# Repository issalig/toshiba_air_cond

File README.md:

# toshiba_air_cond
This project implements functions to decode Toshiba AB protocol from indoor units to wired controllers and provides a hardware design for communication.

Gerbers are available but remember if you improve the design please share it, that's how open source works, if you do not want to share, this project is not for you.

I strongly recommend to use [makusets' board](https://github.com/makusets/esphome-toshiba-ab/tree/main/hardware/D1%20mini) instead of my custom hardware.
My hardware is designed assuming a voltage level of the AB line around 15.6V when "1" and 14V when "0". Different voltage values will not work for writing while reading will work.

In particular, this project has been tested with remote control unit RBC-AMT32E and central unit RAV-SM406BTP-E (http://www.toshiba-aircon.co.uk/assets/uploads/product_assets/20131115_IM_1115460101_Standard_Duct_RAV-SM_6BTP-E_EN.pdf)

You can find the service manual from central unit and wired controller here: http://www.toshibaclim.com/Portals/0/Documentation/Manuels%20produits/SM_Gainable_Std-Compact--DI_406566806110614061606_GB.pdf, https://rednux.com/mediafiles/Hersteller/toshiba/Toshiba-Bedienungsanleitung-RBC-AMT32E-Englisch.pdf

## Index

[Software installation](#Software-installation)

[Web Interface](#Web-Interface)

[Home Assistant & MQTT](#Home-Assistant-&-MQTT)

[Hardware Installation](#Hardware-Installation)

[Custom hardware](#Custom-hardware)

[Data format](#Data-format)

[Message types](#Message-types)

[Other info](#Other-info)
 
# Software installation
[Up](#toshiba_air_cond) [Previous](#Index) [Next](#Hardware-Installation)

Code is developed in PlatformIO for ESP8266 and in particular for Wemos D1 mini board. It is basically a WebServer that serves a webpage and communicates with the client by means of WebSockets. It also offers Home Assistant integration and has nice features usch as OTA updates, file uploading, WifiManager and others.

### Dependencies

This project uses libraries and code from different authors, they are installed automatically from platformio.ini file

- [esp8266](https://github.com/esp8266/Arduino)
- [espsoftwareserial](https://github.com/plerup/espsoftwareserial) by Peter Lerup
- [WiFiManager](https://github.com/tzapu/WiFiManager) by tzapu
- [WebSockets](https://github.com/Links2004/arduinoWebSockets) by Links2004
- [ArduinoJson](https://github.com/bblanchon/ArduinoJson) by Benoit Blanchon
- [Adafruit libraries](https://github.com/adafruit) Adafruit SSD1306, Adafruit GFX Library, adafruit/Adafruit AHTX0 and adafruit/Adafruit BMP280
- LittleFS
- [PubSubClient](https://github.com/knolleary/pubsubclient)
- NTPClient

### Compilation
First things first. Compile it with VSCode and upload it to the board with PlatformIO.

Minimal hardware is ESP8266 and the pcb for adapting signal from serial to AB line. 

- ESP8266 (Wemos D1 Mini R2)
- Toshiba AC serial interface (SoftwareSerial D7=RX, D8=TX)
- Optional I2C sensors (shared bus D1=SCL, D2=SDA):
  - AHT20 (temperature + humidity)  [enabled with `#define USE_AHT20`]
  - BMP280 (temperature + pressure) [enabled with `#define USE_BMP280`]
  - BME280 (temperature + humidity + pressure) [enabled with `#define USE_BME280`]
- Optional OLED 128x64 SSD1306 (I2C D1=SCL, D2=SDA)         [`#define USE_SCREEN`]
- Reset / Config button on D4 (WiFiManager AP)
  
To sum up, the following defines are available and features are disabled by commenting its `#define` in  [config.h](https://github.com/issalig/toshiba_air_cond/blob/master/air/config.h)

- `USE_OTA`      OTA updates
- `USE_SCREEN`   OLED status display
- `USE_MQTT`     MQTT + Home Assistant integration
- `USE_AHT20`    AHT20 sensor support
- `USE_BMP280`   BMP280 sensor support

### WiFi setup
Once you have the code uploaded it is time to configure your WiFi. This project makes use of the great WiFiManager library so there is no need to hardcode your WiFi settings.
- Plug you esp board. It will start blinking.
- Connect to **airAP** wifi network from your cellphone or PC.
- Open a browser and the WifiManager will appear.
- Select your WiFi network and the password.
- If everything is correct, airAP shuts down and board connects to your WiFi.
- Connect to your normal WiFi from computer/cellphone.

### Connect
Now the esp8266 is connected to your network and can be reached as http://air.local

### Upload files
Connect to http://air.local/filemanager, type  and upload it.

This will store index.html file and http://air.local should show the main page.
You can use this endpoint to modify the webpage or add more functionality. If you do it please share.

### Delete files
Similarly to upload page you can use http://air.local/filemanager to delete a file.

### OTA and file update
OTA updates are available, so you do not need to unplug the esp everytime you want to flash it. In the Arduino IDE just set Tools->Port->air at xxx.
If you are using PlatformIO it is done in platform.io
Default OTA password is esp8266

```
; OTA upload configuration
upload_protocol = espota
upload_port = air.local        ; Replace with your device's actual IP from OTAName in config.cpp
upload_flags = --auth=esp8266  ; Replace with your OTA password from OTAPassword varialble in config.cpp
```

If you just want to upload individual files you can use http://air.local/edit.html

# Web Interface
[Up](#toshiba_air_cond) [Previous](#Software-Installation) [Next](#Hardware-Installation)

This section describes the features available through the embedded web interface served by the ESP8266 air conditioning controller.

## Access
- URL via mDNS: `http://air.local` (See `mdnsName` in `config.h`)
- HTTP Port: 80
- WebSocket Port: 81

)

## Main Features
1. Control Functions
   - Power ON / OFF
   - Set target temperature (bounded 16–30 °C; internally enforced 18–30 in MQTT handler)
   - Change mode: `cool`, `heat`, `dry`, `fan_only`, `auto`, `off`
   - Change fan speed: `auto`, `low`, `medium`, `high`
   - Save mode

2. Timer
   - ON/OFF Timer. Software based relying only in esp8266

3. Chart
   - Shows current temperature, external temperature and pressure/humidity if sensors are available.

4. System
   - Info: IP, boot time and decoding errors.
   - Sensors: Internal / External AC sensors.
   - Address: Address configuration for master/remote in case your system uses different from default or you want to install different remotes.
   - Mode: 
    - Autonomous mode indicator: Use it if there is no remote connected (sends pings like remotes). It is necessary to have a temperature sensor to report room temperture.
    - Simulation mode indicator: Simulates a physical AC
   - Admin: Upload files. Use it to upload index.html and others.
5. Debug
    - Send RAW messages to AC, i.e., "00 FE 10 02 80 8A E6"
    - Debug output: Shows serial raw and decoded messages
    - Log

6. MQTT Configuration (if `USE_MQTT`)
   - Runtime modification of: host, port, username, password, device name
   - Persisted to `/mqtt_config.json` in LittleFS

# Home Assistant & MQTT
[Up](#toshiba_air_cond) [Previous](#Web-Interface) [Next](#Hardware-Installation)

If `USE_MQTT` is enabled, the device integrates with Home Assistant using MQTT Discovery.

### Discovery
The device automatically publishes configuration to:
`homeassistant/climate/toshiba_ac/config`

### Manual Configuration / Topics
If discovery is not used, here are the available topics:

| Topic Type | Topic Path | Payload / Description |
|---|---|---|
| **Status** | `homeassistant/ac/status/mode` | `cool`, `heat`, `auto`, `fan_only`, `dry`, `off` |
| **Status** | `homeassistant/ac/status/fan_mode` | `auto`, `high`, `medium`, `low` |
| **Status** | `homeassistant/ac/status/temperature` | Target Temperature (e.g. `22`) |
| **Status** | `homeassistant/ac/status/current_temperature` | Room Temperature (e.g. `21.5`) |
| **Command** | `homeassistant/ac/set/mode` | Set mode (same values as status + `on`/`off`) |
| **Command** | `homeassistant/ac/set/fan_mode` | Set fan speed |
| **Command** | `homeassistant/ac/set/temperature` | Set target temperature |

### Configuration
MQTT settings (Broker, User, Password) can be configured via the Web Interface and are saved to `/mqtt_config.json`. The device status (Power, Mode, Fan, Temperature) is periodically published and updated in real-time when changed via Web or Remote.

# Hardware installation
[Up](#toshiba_air_cond) [Previous](#Home-Assistant-&-MQTT) [Next](#Data-acquisition)

You will need an esp8266, a circuit for adapting signals to esp8266, a USB power supply, a a couple of dupont (female) wires.
- Take out the cover of your remote controller
- Loose the screws of AB terminals. **WARNING**: My PCB assumes A is positive and B is negative. If this is not your case you can damage the PCB. (https://github.com/issalig/toshiba_air_cond/discussions/40#discussioncomment-8149607)
- Pass the wires through the ventilation holes of the cover.
- Insert dupont wires on the terminals and screw them again
- Close the cover
- Connect dupont wires to the pcb (A,B)
- Plug the Wemos D1 mini into the pcb
- Power Wemos with usb cable and the led will start blinking (if you have already programmed it)

Just switch it on/off while you are in bed. If you like it just send me a beer and/or improve the project!

# Data acquisition
[Up](#toshiba_air_cond) [Previous](#Hardware-Installation) [Next](#Custom-hardware)

This is how I managed to decode the information from the AB bus. First I plugged a multimeter to check the range of the signal and not fry anything. Then I used a DS0138 oscilloscope to monitor the signal and to guess voltages and baudrate (a resistor divider is suggested in order to lower the voltage). Later, an 8-channel USB logic analyzer (4-5 USD) can be used to capture data into the computer. **REMEMBER** to convert voltages to 0-3.3v before connecting it to logic analyzer or you will make magic smoke. You can use the read circuit below.

To capture data you can use pulseview with uart decoder 2400 bps, 8bits, start, stop, EVEN parity

In case you need it you can install the following packages
```
sudo apt install sigrok-cli
sudo apt install sigrok-firmware-fx2lafw
```

When the data has been validated visually you can use the following command line that reads RX data annotations and print one message per line according to 4th byte (message size).

```
sigrok-cli -P uart:rx=D0:baudrate=2400:parity_type=even -A uart=rx_data -i  YOURFILE  | awk '{pad =" "; b[len%4]=$2; if(len==3) {bytes="0x"b[len];  printf("%s%s%s%s%s%s%s%s",b[0],pad,b[1],pad,b[2],pad,b[3],pad)} if(len>3) {printf("%s%s",$2,pad);} len=len+1; if(len==4+bytes+1) {print "";len=0;bytes=0}}'
```

```
sigrok-cli -d fx2lafw -c samplerate=250000 -t D0=r -P uart:rx=D0:baudrate=2400:parity_type=even  -A uart=rx_data --continuous
```

# Custom hardware
[Up](#toshiba_air_cond) [Previous](#Data-acquisition) [Next](#Data-format)

Note: I strongly recommend to use [makusets board](https://github.com/makusets/esphome-toshiba-ab/tree/main/hardware/D1%20mini) instead of my custom hardware.
My hardware is designed assuming a voltage level of the AB line around 15.6V when "1" and 14V when "0". Different voltage values will not work for writing while reading will work.

I have designed some circuits to read and write the signal

## Read
I will use an optocoupler because it simplifies things and also isolates microcontroller from the rest of the system.

- Air conditioning side:
Voltage is around 15.6 volts when "1" and 14 when "0". A zener diode in reversed position provides 13V reference given that voltage is in the range [14, 15.6] and is > 13V. Thus, the signal is now in the range [1V, 2.6V]. Then, after diode 1N4001 (0.7V drop) voltage is 0.3V .. 1.9V, enough to activate the photodiode (1.2V) when "1" and to not activate it when "0".

IR led from optocouple drops 1.2v, and from signal we have a difference of 15.6V-13V=2.6V, thus 2.6V-1.2V=1.4V/100ohm = 14mA which has a maximum CTR=140%
Ic=3.3, If=14
CTR=Ic/If

```
Type     VZnom  IZT  for  rzjT    rzjk  at  IZK    IR  at  VR
1N4743A  13     19        <10     <100      0.25   <5      9.9
```

Now, let's calculate the resistor value
Izt=19 mA -> 2.6/19=130ohm  P=VI 2.6*19 =52mW

- Microcontroller side: 1k resistor limits the current. ESP8266 max current is 12mA > 3.3/1k = 3.3 mA

```
Air                                         Microcontroller
Conditioner

                          1N4001  _______
  A ---------+----100R ---->|----|       |-------3v3
             |                   | PC817 |
            10k                  |       |
             |                   |       |
  B --->|----+-------------------|_______|------ OUT               
                                             |
     zener 13v                              1k
      1N4743A                                |
                                            GND
             
```

## Write

Write circuit performs similarly to read circuit. 
- When OUT signal is "1", transistor and pullup resistor are "0", thus optocoupler is OFF and voltage is 15.6 (HIGH). 
- When OUT signal is 0, transistor is off and pullup resistor sends 1 and activates optocoupler and zener diode gives 13V (LOW).
Some systems recommend to set the Follower in the remote unit.

Here I attach the datasheets of the components.
https://www.onsemi.com/pub/Collateral/P2N2222A-D.PDF 
https://learnabout-electronics.org/Downloads/PC817%20optocoupler.pdf

```

              3v3                                    1N4001
               |                             |-----+---|<------- A               
              200                 _______    |     |               
               ------------------|       |---|     ^ zener 13v
               /                 | PC817 |         /
 OUT --1k- ---|   2N2222     |---|_______|---1k---| 2N2222
               \             |                     \
               |             |                     |
              GND           GND                    ------------- B

```

## Plan B. (In fact it was plan A but then I managed to decode AB protocol, yeah!)

To solder wires to button pads on the remote controller and close circuit to simulate pressing them (with and optocoupler).

``` 
                       _________
    uc OUT --- 200R----| PC817 |------- PAD+
                 GND---|_______|---4k7--PAD-
                                  
```

ESP8266 high level is 3v3 and the maximum current per pin is 12mA (but we will go safer with 10mA). Thus, the resistor for the IR diode of the optocoupler is 3.3-1.2/10=210 -> 200 ohm. 4k7 is a safe value since we just want continuity.

Following traces from button pads end in 2k resistors that we will use to solder wires. As R46 is common, we can think is button GND
ON button is connected to R25 and R46
Temp down button is connected to R23 adn R46
Temp up button is connected to R24 and R46

# Data format
[Up](#toshiba_air_cond) [Previous](#Custom-hardware) [Next](#Message-types)

Data packages have the following format:

|Source | Dest | Opcode 1  | Data Length | R/W mode | Opcode 2 | Payload | CRC |
|---|---|---|---|---|---|---|---|

Source/Dest (1 byte): 
|#|Description|
|---|---|
|00 | master (central unit) |
|40 | remote controller in the range [0x40..] |
|FE | broadcast |
|F0 | Group
|52 | ?? |

Data length (1 byte)
- Length of data field

R/W mode (1 byte)
|Mode|Desc|
|---|---|
|08 |for Write mode (from remote 40)|
|80 |for Read mode (from master 00)|

Payload can be empty such as in ping message 00 FE 10 02 80 8A E6.

CRC is computed as Checksum8 XOR of all the bytes (Compute it at https://www.scadacore.com/tools/programming-calculators/online-checksum-calculator/)

OpCode1 (byte 2)  indicates the function of the message and OpCode2 (byte 5) specifies the feature or register being targeted.

| OpCode1 | Description | Type | Example |
|---|---|---|---|
| `10` | Ping / Alive | `MSG_MASTER_ALIVE` | `00 FE 10 02 80 8A E6` |
| `11` | Write / Control | `MSG_POWER`, `MSG_SET_...` | `40 00 11 03 08 41 03 18` |
| `15` | Request / Query | `MSG_MODEL_REQUEST`... | `40 F0 15 02 00 08 AF` |
| `17` | Sensor Query | `MSG_SENSOR_QUERY` | `40 00 17 08 08 80 EF 00 2C 08 00 02 1E` |
| `18` | Response / Report | `MSG_MODEL_ANSWER`... | `00 40 18 14 80 08 52 41 56 2d 53 4d 31 31 30 36 42 54 50 2d 45 20 03 37 8e` |
| `1A` | Sensor Answer | `MSG_SENSOR_ANSWER` | `00 40 1A 07 80 EF 80 00 2C 00 2B B5` |
| `1C` | Status | `MSG_STATUS` | `00 FE 1C 0D 80 81 8D AC 00 00 76 00 33 33 01 00 01 B9` |
| `52` | Remote Start | - | - |
| `55` | Remote Temp | `MSG_REMOTE_SENSOR_TEMP` | `40 00 55 05 08 81 00 69 00 F0` |
| `58` | Ext. Status | `MSG_STATUS_EXT` | `00 FE 58 0F 80 81 34 A8 00 00 6C 6D E9 00 55 55 01 00 01 DC` |

| OpCode2 | Description | Type | Example |
|---|---|---|---|
| `02` | DN Codes | `MSG_DN_CODE` | `40 00 15 05 08 02 F5 00 01 AE` |
| `07` | Save Ratio | `MSG_SAVE_RATIO_...` | `00 40 18 03 80 07 4B 97` |
| `08` | Model Info | `MSG_MODEL_...` | `00 40 18 14 80 08 52 41 56 2d 53 4d 31 31 30 36 42 54 50 2d 45 20 03 37 8e` |
| `0A` | Temp Limits | `MSG_TEMP_LIMITS` | `00 40 18 10 80 0A 00 2F 0F 80 6A 80 6A 80 6A 80 6A 04 56 00 B0` |
| `0C` | Pong / Ping | `MSG_REMOTE_PING` | `40 00 15 07 08 0C 81 00 00 48 00 9F` |
| `0D` | Announce | `MSG_ANNOUNCE` | `40 F0 15 02 00 0D AA` |
| `0F` | Setpoints | `MSG_SETPOINT` | `00 40 18 09 80 0F 7A 74 78 78 25 52 05 A2` |
| `10` | Fan Caps | `MSG_FAN_MODES_...` | `00 40 18 0E 80 10 00 35 33 35 33 35 33 35 33 00 00 00 C6` |
| `27` | Errors | `MSG_SENSOR_ERROR` | `00 40 18 05 80 27 08 00 48 BA` |
| `41` | Power | `MSG_POWER` | `40 00 11 03 08 41 03 18` |
| `42` | Mode | `MSG_SET_MODE` | `40 00 11 03 08 42 01 19` |
| `4C` | Temp/Fan | `MSG_SET_TEMP_FAN` | `40 00 11 08 08 4C ...` |
| `54` | Save | `MSG_SAVE` | `40 00 11 04 08 54 01 01 09` |
| `80` | Sensor ID | `MSG_SENSOR_QUERY` | `40 00 17 08 08 80 EF 00 2C 08 00 02 1E` |
| `81` | Status | `MSG_STATUS` | `00 FE 1C 0D 80 81 8D AC 00 00 76 00 33 33 01 00 01 B9` |
| `86` | Mode Stat | `MSG_STATUS_MODE` | `00 52 11 04 80 86 84 01 C4` |
| `8A` | Alive | `MSG_MASTER_ALIVE` | `00 FE 10 02 80 8A E6` |
| `A1` | ACK | `MSG_MASTER_ACK` | `00 40 18 02 80 A1 7B` |
| `A3` | Busy | `MSG_MASTER_BUSY` | `00 40 18 02 80 A3 79` |
| `E8` | Time | `MSG_TIME_COUNTER` | `40 00 15 06 08 E8 00 01 00 9E 2C` |
| `EF` | Sensor Val | `MSG_SENSOR_ANSWER` | `00 40 1A 07 80 EF 80 00 2C 00 2B B5` |

# Message types

[Up](#toshiba_air_cond) [Previous](#Data-format) [Next](#Other-info)

The protocol relies on a command/response structure. Most control commands are sent by the Remote (0x40), and the Master (0x00) responds with status updates or acknowledgments.

Temperatures are coded with the formula: `(Value >> 1) - 35`. That is, for a value of `0x78`, the temperature is `(0x78 >> 1) - 35 = 120/2 - 35 = 60 - 35 = 25°C`.

## 1. Control Commands (Remote -> Master)
These commands control the state of the AC unit.

| Command | OpCode 1 | OpCode 2 | Type | Data Structure (Example) | Description |
|---|---|---|---|---|---|
| **Power** | `11` | `41` | `MSG_POWER` | `40 00 11 03 08 41 [Value] [CRC]`  | `Value`: `03`=ON, `02`=OFF |
| **Mode**  | `11` | `42` | `MSG_SET_MODE` | `40 00 11 03 08 42 [Mode] [CRC]` | `Mode`: `01`=Heat, `02`=Cool, `03`=Fan, `04`=Dry, `05`=Auto |
| **Temp/Fan**| `11` | `4C` | `MSG_SET_TEMP_FAN` | `40 00 11 08 08 4C [Mode+] [Fan+]...` | Combined Setpoint (Temp, Fan, Mode) |
| **Save** | `11` | `54` | `MSG_SAVE` | `40 00 11 04 08 54 01 [Value] [CRC]` | `Value`: `01`=ON, `00`=OFF |
| **Ping** | `15` | `0C 81` | `MSG_REMOTE_PING` | `40 00 15 07 08 0C 81 00 00 48 00 9F` | Keep-alive / check presence |
| **Timer** | `11` | `0C 82` | - | `40 00 11 09 08 0C 82 00 00 30 05 01 01 EB` | Timer settings |
| **Req. DN** | `15` | `02` | `MSG_DN_CODE_REQUEST` | `40 00 15 05 08 02 F5 00 01 AE` | Request DN Code value. `Code` in byte 6 |
| **Save Ratio** | `15` | `07` | `MSG_SAVE_RATIO_REQUEST` | `40 00 15 04 08 07 00 C2 9C` | Request power save ratio |
| **Model** | `15` | `08` | `MSG_MODEL_REQUEST` | `40 00 15 02 08 08 AF` | Request model information |
| **Limits** | `15` | `0A` | `MSG_TEMP_LIMITS_REQUEST` | `40 00 15 02 08 0A 55` | Request temp limits |
| **Features** | `15` | `0D` | `MSG_ANNOUNCE` | `40 F0 15 02 00 0D AA` | Announce / Request features |
| **Setpoints** | `15` | `0F` | `MSG_SETPOINT_REQUEST` | `40 00 15 02 08 0F 50` | Request setpoints |
| **Fan Caps** | `15` | `10` | `MSG_FAN_MODES_REQUEST` | `40 00 15 02 08 10 4F` | Request fan capabilities |
| **Time Cnt** | `15` | `E8` | `MSG_TIME_COUNTER` | `40 00 15 06 08 E8 00 01 00 9E 2C` | Request time counter (?) |
| **Sensor Query**| `17` | `80` | `MSG_SENSOR_QUERY` | `40 00 17 08 08 80 EF 00 2C 08 00 02 1E` | Request specific sensor value |
| **Remote Temp** | `55` | `81` | `MSG_REMOTE_SENSOR_TEMP` | `40 00 55 05 08 81 00 [Val] 00 [CRC]` | Temperature in byte 7|

**Temperature and Fan Speed (OpCode 4C) Breakdown:**
The `4C` packet is used when changing Temperature or Fan Speed. It contains multiple state variables.
`40 00 11 08 08 4C [Byte6] [Byte7] [Byte8] 00 [ModeCheck] [ModeCheck] [CRC]`
*   **Byte 6 (Mode)**: `0x10` + Mode (`02`=Cool, `01`=Heat, etc.)
*   **Byte 7 (Fan)**: `0x18` + Fan (`0`=Auto, `1`=High, `2`=Med, `5`=Low) -> *Note: bitmasks vary*
*   **Byte 8 (Temp)**: `((TargetTemp + 35) << 1)`
*   **ModeCheck**: `0x33` for Cool/Dry/Fan/Auto, `0x55` for Heat.

## 2. Status Reports & Answers (Master -> Remote)
The Master unit periodically broadcasts its status or responds to specific queries.

| Message | OpCode 1 | OpCode 2 | Type | Data Structure (Example) | Description |
|---|---|---|---|---|---|
| **Status** | `1C` | `81` | `MSG_STATUS` | `00 FE 1C 0D 80 81 8D AC 00 00 76 00 33 33 01 00 01 B9` | Standard periodic status (Power, Mode, Fan, RoomTemp) |
| **Ext. Status**| `58` | `81` | `MSG_STATUS_EXT` | `00 FE 58 0F 80 81 34 A8 00 00 6C 6D E9 00 55 55 01 00 01 DC` | Extended status (Filter, Preheat, Errors, Extra Temps) |
| **Alive** | `10` | `8A` | `MSG_MASTER_ALIVE` | `00 FE 10 02 80 8A E6` | Frequent Keep-Alive broadcast from Master |
| **ACK** | `18` | `A1` | `MSG_MASTER_ACK` | `00 40 18 02 80 A1 7B` | Acknowledgment after a valid setting change |
| **Busy** | `18` | `A3` | `MSG_MASTER_BUSY` | `00 40 18 02 80 A3 79` | Master is busy processing command |
| **Pong** | `18` | `0C` | `MSG_MASTER_PONG` | `00 40 18 08 80 0C 00 03 00 00 48 00 97` | Response to Remote Ping |
| **Mode Stat**| `11` | `86` | `MSG_STATUS_MODE` | `00 52 11 04 80 86 84 01 C4` | Mode confirmation |
| **DN Code** | `18` | `02` | `MSG_DN_CODE` | `00 40 18 07 80 02 01 02 05 00 00 DB` | Response with DN Code value |
| **Save Ratio**| `18` | `07` | `MSG_SAVE_RATIO_ANSWER` | `00 40 18 03 80 07 4B 97` | Response with power save ratio |
| **Model** | `18` | `08` | `MSG_MODEL_ANSWER` | `00 40 18 14 80 08 52 41 56 2d 53 4d 31 31 30 36 42 54 50 2d 45 20 03 37 8e` | Response with model string |
| **Limits** | `18` | `0A` | `MSG_TEMP_LIMITS` | `00 40 18 10 80 0A 00 2F 0F 80 6A 80 6A 80 6A 80 6A 04 56 00 B0` | Response with temp limits |
| **Features** | `18` | `0D` | `MSG_FEATURES` | `00 40 18 12 80 0D 08 00 FE FE FE FE FE FE FE FE FE FE FE FE FE FE CD` | Response with supported features |
| **Setpoints** | `18` | `0F` | `MSG_SETPOINT` | `00 40 18 09 80 0F 7A 74 78 78 25 52 05 A2` | Response with setpoints |
| **Fan Caps** | `18` | `10` | `MSG_FAN_MODES_ANSWER` | `00 40 18 0E 80 10 00 35 33 35 33 35 33 35 33 00 00 00 C6` | Response with fan capabilities |
| **Errors** | `18` | `27` | `MSG_SENSOR_ERROR` | `00 40 18 05 80 27 08 00 48 BA` | Error history report |
| **Time Cnt** | `18` | `E8` | `MSG_TIME_COUNTER_ANSWER` | `00 40 18 07 80 E8 00 01 00 01 83 B4` | Response with time counter |
| **Sensor** | `1A` | `EF` | `MSG_SENSOR_ANSWER` | `00 40 1A 07 80 EF 80 00 2C 00 2B B5` | Response with sensor value |

**Status Packet (OpCode 1C):**
`00 FE 1C 0D 80 81 [D1] [D2] 00 00 [Temp] 00 [Chk] [Chk] [Sv] 00 [Pwr] [CRC]`
*   **D1 (Mode)**: Mode is in bits 7-5. `0x80` mask often seen.
*   **D2 (Fan)**: Fan speed in bits 7-5.
*   **Temp**: `((Value >> 1) - 35)` = Room Temperature.
*   **Sv (Save)**: Bit 0 indicates Save Mode.
*   **Pwr**: Bit 0 indicates Power (1=ON).

## 3. Remote Announce Protocol

### 1. Announce / Discovery (Remote -> System)
In the master bootup process (you need to switch off and on the master), the remote controller sends an **Announce** message to the broadcast address (`0xF0`).
*   **Message**: `40 F0 15 02 00 0D AA`
    *   **Source**: `0x40` (Remote)
    *   **Dest**: `0xF0` (Discovery / Broadcast)
    *   **OpCode**: `15` (Request) ... `0D` (Announce)

If the master is busy it will respond with `MSG_MASTER_BUSY`
*   **Message**: `00 40 18 02 80 A3 79`
    *   **Source**: `0x00` (Master)
    *   **Dest**: `0x40` (Remote)
    *   **OpCode**: `18` (Response) ... `A3` (Busy) 

otherwise it will respond with `MSG_FEATURES` and that means the remote is linked. **Take into account that for the remote to work it needs to be linked to the master.** This is not necessary if you already have a remote linked to the master (i.e. your RBC-AMT32E).
*   **Message**: `00 40 18 12 80 0d 08 00 fe fe fe fe fe fe fe fe fe fe fe fe fe fe cf`
    *   **Source**: `0x00` (Master)
    *   **Dest**: `0x40` (Remote)
    *   **OpCode**: `18` (Response) ... `0D` (Features)
    *   **Payload**: `0x12` (18 bytes)
    *   **Data**: The sequence `FE FE...` likely represents a bitmap of supported features (modes, fan speeds, louvers, etc.) enabled on the indoor unit.

After the reception of `MSG_FEATURES` the remote will ask for the following information:
* Model info
* Temperature Limits
* Capabilities
* Power Save Ratio
* Current Setpoint

**Model**:
*   Request: `40 F0 15 02 00 08 AF`
*   Response: `00 00 18 0D 00 08 [Model String] [CRC]` (e.g. `RAV-SM406...`)

**Temperature Limits**:
*   Request: `40 00 15 02 08 0A 55`
*   Response: `00 40 18 10 80 0A 00 2F 0F 80 6A 80 6A 80 6A 80 6A 04 56 00 B0` (Example)
    *   Byte 9: Max Temp (`0x80` -> 29°C)
    *   Byte 10: Min Temp (`0x6A` -> 18°C)
    *   Byte 17: Frost Protection Flag (`0x04` = Enabled)
    *   Byte 18: Frost Protection Temp (`0x56` -> 8°C)
    *   Formula: `(Value >> 1) - 35`

**Power Save Ratio**:
*   Request: `40 00 15 04 08 07 00 C2 9C`
*   Response: `00 40 18 03 80 07 4B 97` (Value: 0x4B = 75%)

**Current Setpoint**:
*   Request: `40 00 15 02 08 0F 50`
*   Response: `00 40 18 09 80 0F 7A 74 78 78 25 52 05 A2` (Example)
    *   Bytes 6-9: Default temperatures for Auto, Heat, Dry, Cool.
    *   Formula: `(Value >> 1) - 35`
    *   Example Values:
        *   Auto: `0x7A` -> 26°C
        *   Heat: `0x74` -> 23°C
        *   Dry:  `0x78` -> 25°C
        *   Cool: `0x78` -> 25°C

**Capabilities**: This message is still UNDER STUDY, so it is not yet clear what the values mean.
*   Request: `40 00 15 02 08 10 50`
*   Response: `00 40 18 0E 80 10 00 35 33 35 33 35 33 35 33 00 00 00 C6` (Example)
    *   Bytes 6-9: ??.

**Time Sync / Counter**:
*   Message: `40 00 15 06 08 E8 00 01 00 9E 2C` (Sent every minute by Remote in some units)

## 4. Sensor & Maintenance

**Query Sensor**: Request specific sensor ID (see Sensor Addresses)
*   Request: `40 00 17 08 08 80 ef 00 2c 08 00 [SENSOR] [CRC]`
    * Opcode 17 80
    * Byte 11: Sensor ID
*   Response: `00 40 1A 07 80 EF 80 00 2C [ValH] [ValL] [CRC]`
    * Opcode 1A EF
    * Byte 9: High Byte
    * Byte 10: Low Byte
    * Value: `(Byte9 << 8) | Byte10`
    * If `Value == 0xA2`, the value is undefined.

# Sensor addresses

| No.  | Desc  |
|---|---|---|
| 00 | Room Temp (Control Temp) (°C) |
| 01 | Room temperature (remote controller) |
| 02 | Indoor unit intake air temperature (TA) |
| 03 | Indoor unit heat exchanger (coil) temperature (TCJ) Liquid |
| 04 | Indoor unit heat exchanger (coil) temperature (TC) Vapor |
| 07 | Indoor Fan Speed|  |
| 60 | Outdoor unit heat exchanger (coil) temperature (TE) |
| 61 | Outside air temperature (TO)| |
| 62 | Compressor discharge temperature (TD) |
| 63 | Compressor suction temperature (TS) |
| 65 | Heatsink temperature (THS) |
| 6a | Operating current (x1/10) |
| 6d | TL Liquid Temp (°C) |
| 70 | Compressor Frequency (rps)| |
| 72 | Fan Speed (Lower) (rpm) |
| 73 | Fan Speed (Upper) (rpm) |
| f1 | Compressor cumulative operating hours (x100 h) |
| f2 | Fan Run Time (x 100h) |
| f3 | Filter sign time x 1h | 
| f8 | Indoor Discharge Temperature |

## 5. DN Codes
DN Codes are configuration settings for the Toshiba AC unit. Here only read functionality is described.

### Request
The specific DN code is requested using OpCode `15 02`.

`40 00 15 05 08 02 [Mode] [Code] [Offset] [CRC]`

*   **Mode**: Defines the traversal method.
    *   `0xF5`: Request **Current** specific code.
    *   `0xF1`: Request **Next** available code.
    *   `0xF2`: Request **Previous** available code.
*   **Code**: DN Code address
*   **Offset**: Typically `0x00` for current, `0x01` for next/prev.

### Response
The Master returns the value for the DN code.

`00 40 18 07 80 02 [RefCode] [Value] [Unk1] [Unk2] [Unk3] [CRC]`

*   **RefCode** (Byte 6): Often points to the *next* code or context.
*   **Value** (Byte 7): The value of the requested DN Code.
*   **Unk1-3**: Unknown data (possibly related to min/max or permissions).

**Example**:
*   Request: `40 00 15 05 08 02 f5 01 00 ae` (Request Code 01)
    *   Response: `00 40 18 07 80 02 01 02 05 00 00 db`
    *   Here, Byte 7 (`0x02`) is the value. Byte 6 (`0x01`) is current code given F5 "current" mode was used.

### DN Codes List
These codes define various configuration parameters.

| Code | Description |
|---|---|
| `01` | Filter alarm time |
| `02` | Dirty state |
| `03` | Central ctl address |
| `04` | Specific indoor priority |
| `05` | Fan control heating |
| `06` | Heating temp shift |
| `0C` | Preparing indication |
| `0D` | Auto mode existence |
| `0E` | FS Box |
| `0F` | Heat mode |
| `10` | Type |
| `11` | Indoor unit capacity |
| `12` | System address |
| `13` | Indoor unit address |
| `14` | Group master/slave |
| `16` | Indoor fan speed |
| `1E` | Dead band |
| `1F` | Max set temp cool |
| `20` | Min set temp cool |
| `21` | Max set temp heat |
| `22` | Min set temp heat |
| `23` | Max set temp dry |
| `24` | Min set temp dry |
| `25` | Max set temp auto |
| `26` | Min set temp auto |
| `28` | Auto restart |
| `2A` | CN70 |
| `2E` | CN61 |
| `31` | External fan control |
| `32` | TA sensor (0 Body, 1 Remote) |
| `33` | Temperature unit (0 C, 1 F) |
| `45` | Anti-smudge louver |
| `49` | 24h ventilation |
| `4C` | Night purge |
| `5D` | Standard ducted |
| `60` | Timer set |
| `62` | Anti-smudge fan speed |
| `69` | Louver position |
| `77` | Dust set point |
| `86` | Correction strong heating |
| `88` | Air direction setting |
| `9A` | Fan control cooling |
| `9B` | Hot start |
| `D0` | Power saving |
| `F0` | Swing mode |
| `F1` | Louver 1 |
| `F2` | Louver 2 |
| `F3` | Louver 3 |
| `F4` | Louver 4 |
| `F6` | Application ctl kit |
| `FE` | Group control |

# TO-DOS
[Up](#toshiba_air_cond) [Previous](#Message-types) [Next](#Other-info)

- Improve PCB

- Fix PCB: jumper for Hardware or Software Serial

- Fix parsing to support round buffer and not to loose partial frames (not necessary)

- Clearer Protocol documentation

- Check other circuits as:80
  - https://easyeda.com/marcegli/door-opener
  - https://frog32.ch/smart-intercom.html 
  - https://electronics.stackexchange.com/questions/458996/logic-level-converter-for-nodemcu-esp8266-input-24v-16v-hi-lo-500-baud 
  - https://sudonull.com/post/18480-We-pump-the-intercom-with-the-MQTT-protocol-to-control-from-the-phone
  - https://hackaday.com/2019/01/07/building-an-esp8266-doorbell-on-hard-mode/
  - https://daeconsulting.co.za/2018/12/17/theres-someone-at-the-door/

- Announce project in other similar ones
  - https://github.com/ToniA/arduino-heatpumpir/
  - https://github.com/openenergymonitor
  - https://github.com/roarfred/AmsToMqttBridge
  - https://github.com/dgoodlad/esp8266-mitsubishi-aircon
  - https://github.com/H4jen/webasto_sniffer

# Other info
[Up](#toshiba_air_cond) [Previous](#Message-types)

If you want to know about error codes and sensor addresses you can check the following links.
http://www.toshiba-aircon.co.uk/assets/uploads/pdf/sales_tools/Technical_Handbook_ver._13.1.pdf
https://www.cdlweb.info/wp-content/uploads/2020/10/1-CDL-Toshiba-R32-Technical-Handbook-V10-2020.pdf
https://www.toshibaclim.com/Portals/0/Documentation/Manuels%20produits/SM_CassetteUTP_DI-SDI-111416-E_GB.pdf

I found this projects interesting even that it is not the same protocol https://github.com/H4jen/webasto_sniffer
https://echonet.jp/wp/wp-content/uploads/pdf/General/Standard/Release/Release_F_en/SpecAppendixF_e.pdf

Info about commercial gateways but no info about protocol :(

Connections https://www.toshibaclim.com/Portals/0/Documentation/Manuels%20produits/SM_CassetteUTP_DI-SDI-111416-E_GB.pdf
Sensor addresses (pg 52) http://www.toshiba-aircon.co.uk/assets/uploads/pdf/sales_tools/New_Technical_Handbook_version_14_1_3.pdf
Sensor addresses (pg 73) https://www.toshibaclim.com/Portals/0/Documentation/Manuels%20produits/SM_CassetteUTP_DI-SDI-111416-E_GB.pdf
Sensor addresses (pg 42) http://www.toshiba-aircon.co.uk/assets/uploads/pdf/sales_tools/Technical_Handbook_ver._13.1.pdf

Error codes from Toshiba (pg 38) https://cdn.shopify.com/s/files/1/1144/2302/files/BP-STD_Toshiba_v1_08.pdf
Temperature formula TCS-Net https://www.toshibaheatpumps.com/application/files/8914/8124/4818/Owners_Manual_-_Modbus_TCB-IFMB640TLE_E88909601.pdf
https://www.toshibaheatpumps.com/customer-support/owner-manuals
https://www.intesisbox.com/intesis/product/media/intesisbox_to-ac-knx-16-64_user_manual_en.pdf?v=2.2

The unit where I have tested the project is model RAV-SM406BTP-E  which stands for

```
RAV-SM406BTP-E 
|     | |    |- CE marking
|     | ||-Duct
|     | |-gen
|     |-duty 4.0 kW 
|   |-Digital inverter
|- Light comercial
```

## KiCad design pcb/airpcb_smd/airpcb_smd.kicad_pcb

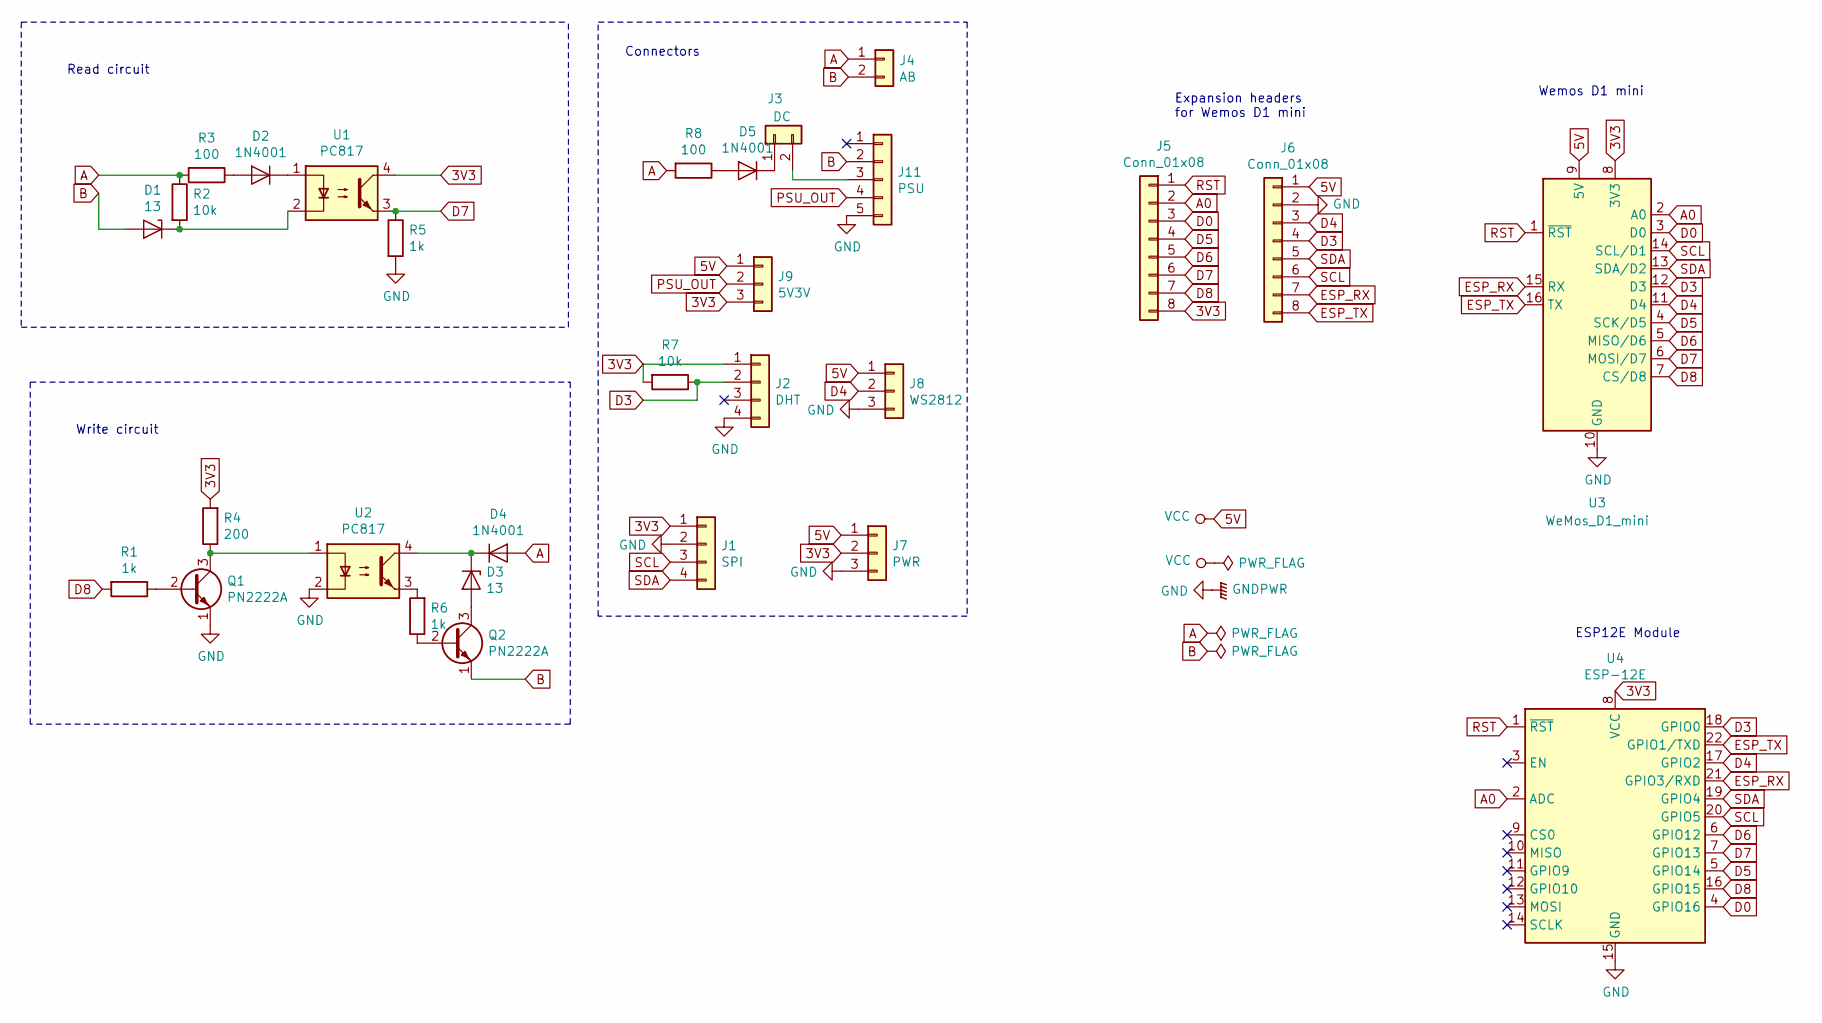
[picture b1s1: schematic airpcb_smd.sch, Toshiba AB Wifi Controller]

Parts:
D1, D3: 13; D_MiniMELF_Handsoldering
D2, D4, D5: 1N4001; D_SMA
J1: SPI; PinSocket_1x04_P2.54mm_Vertical
J2: DHT; PinSocket_1x04_P2.54mm_Vertical
J3: DC; PinSocket_1x02_P2.54mm_Vertical
J4: AB; PinSocket_1x02_P2.54mm_Vertical
J5, J6: Conn_01x08; PinSocket_1x08_P2.54mm_Vertical
J7: PWR; PinSocket_1x03_P2.54mm_Vertical
J8: WS2812; PinSocket_1x03_P2.54mm_Vertical
J9: 5V3V; PinSocket_1x03_P2.54mm_Vertical
J11: PSU; HW-108
Q1, Q2: PN2222A; SOT-23_Reverse_Handsoldering
R1, R5, R6: 1k; R_0805_2012Metric
R2, R7: 10k; R_0805_2012Metric
R3, R8: 100; R_0805_2012Metric
R4: 200; R_0805_2012Metric
U1, U2: PC817; DIP-4_W7.62mm
U3: WeMos_D1_mini; WEMOS_D1_mini_light
U4: ESP-12E

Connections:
3V3: J1.1, J2.1, J5.8, J7.2, J9.3, R4.2, R7.2, U1.4, U3.8 (3V3), U4.8 (VCC)
5V: J6.1, J7.1, J8.1, J9.1, U3.9 (5V)
A: D4.2 (A), J4.1, R2.1, R3.2, R8.2
A0: J5.2, U3.2 (A0), U4.2 (ADC)
B: D1.2 (A), J4.2, J11.2, Q2.1 (E)
D0: J5.3, U3.3 (D0), U4.4 (GPIO16)
D3: J2.2, J6.4, R7.1, U3.12 (D3), U4.18 (GPIO0)
D4: J6.3, J8.2, U3.11 (D4), U4.17 (GPIO2)
D5: J5.4, U3.4 (SCK/D5), U4.5 (GPIO14)
D6: J5.5, U3.5 (MISO/D6), U4.6 (GPIO12)
D7: J5.6, R5.1, U1.3, U3.6 (MOSI/D7), U4.7 (GPIO13)
D8: J5.7, R1.2, U3.7 (CS/D8), U4.16 (GPIO15)
ESP_RX: J6.7, U3.15 (RX), U4.21 (GPIO3/RXD)
ESP_TX: J6.8, U3.16 (TX), U4.22 (GPIO1/TXD)
GND: J1.2, J2.4, J6.2, J7.3, J8.3, J11.5, Q1.1 (E), R5.2, U2.2, U3.10 (GND), U4.15 (GND)
unnamed: D1.1 (K), R2.2, U1.2
unnamed: D2.1 (K), U1.1
unnamed: D2.2 (A), R3.1
unnamed: D3.1 (K), D4.1 (K), U2.4
unnamed: D3.2 (A), Q2.3 (C)
unnamed: D5.1 (K), J3.1
unnamed: D5.2 (A), R8.1
unnamed: J3.2, J11.3
unnamed: Q1.2 (B), R1.1
unnamed: Q1.3 (C), R4.1, U2.1
unnamed: Q2.2 (B), R6.1
unnamed: R6.2, U2.3
PSU_OUT: J9.2, J11.4
RST: J5.1, U3.1 (~RST), U4.1 (~RST)
SCL: J1.3, J6.6, U3.14 (SCL/D1), U4.20 (GPIO5)
SDA: J1.4, J6.5, U3.13 (SDA/D2), U4.19 (GPIO4)

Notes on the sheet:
Read circuit
Write circuit
Connectors
ESP12E Module
Wemos D1 mini
Expansion headers for Wemos D1 mini

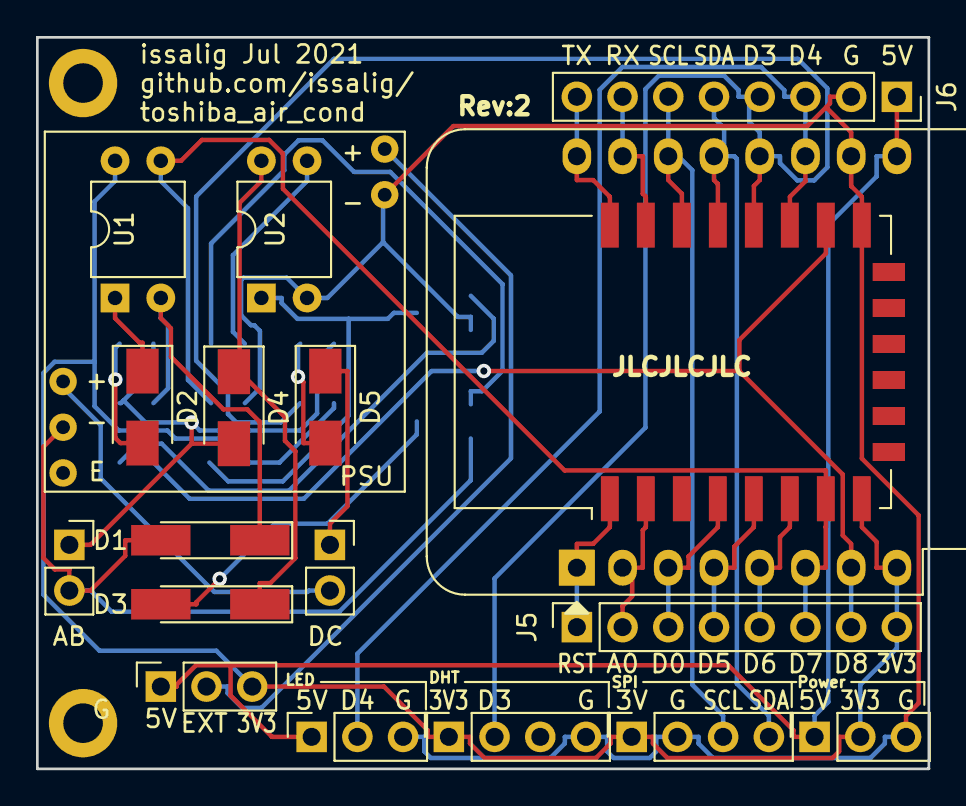
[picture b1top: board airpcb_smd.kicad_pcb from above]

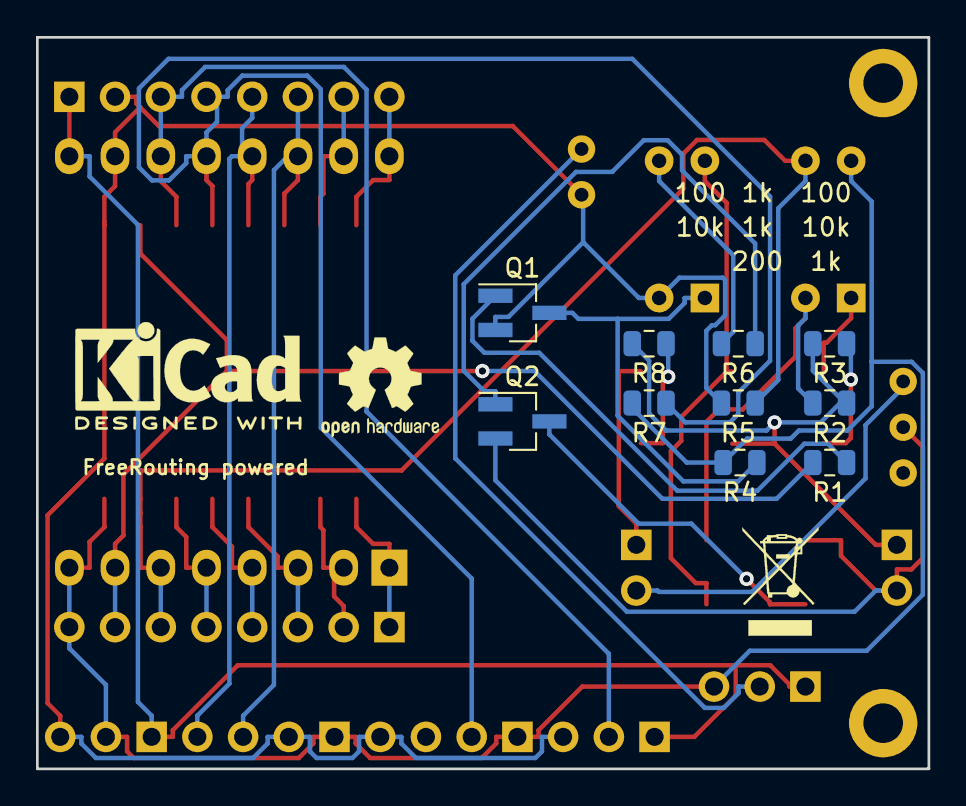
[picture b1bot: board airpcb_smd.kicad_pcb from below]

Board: 2 copper layers, 49.5 x 40.6 mm, 34 parts (13 on the bottom side), 31 nets.

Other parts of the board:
L1: KiCad-Logo2_5mm_SilkScreen
L2: OSHW-Logo2_7.3x6mm_SilkScreen
L3: WEEE-Logo_4.2x6mm_SilkScreen
M1, M2: MountingHole_2.2mm_M2_DIN965_Pad

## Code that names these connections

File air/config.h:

#ifndef CONFIG_H
#define CONFIG_H

#define AIR_VERSION "2.1"

//pins for wemos d1 mini
//D1: GPIO5/SCL,   D2: GPIO4/SDA,   D3: GPIO0/FLASH, D4: GPIO2, 
//D5: GPIO14/SCLK, D6: GPIO12/MISO, D7: GPIO13/MOSI, D8: GPIO15/CS

// enter into wifi configuration mode
#define RESET_MODE_PIN 2  //D4 GPIO2

//tx rx pins for software serial to communicate with AC unit
#define TX_PIN 15  //D8 GPIO15
#define RX_PIN 13  //D7 GPIO13

//i2c pins
#define I2C_SDA_PIN 4 //D2 GPIO4
#define I2C_SCL_PIN 5 //D1 GPIO5

#define MAX_LOG_DATA 72 //store up to 72 readings in a circular buffer

//#define USE_ASYNC // Use AsyncWebServer
#define USE_OTA
#define USE_SCREEN //if OLED screen installed
#define USE_MQTT // for Home Assistant integration

#define USE_AHT20     // Enable AHT20 temperature & humidity sensor
#define USE_BMP280    // Enable BMP280 temperature & pressure sensor (replaces BMP085)
#define USE_BME280    // Enable BME280 temperature, humidity & pressure sensor

//wifi credentials, no needed because now we use WiFiManager
extern const char* w_ssid;
extern const char* w_passwd;

//Over the air (OTA) credentials
extern const char* OTAName;
extern const char* OTAPassword;

// Domain name for the mDNS responder. Just connect to air.local
extern const char* mdnsName;

// Compile date and time
extern const char compile_date[];

// screen
#define SCREEN_WIDTH 128 // OLED display width, in pixels
#define SCREEN_HEIGHT 64//32 // OLED display height, in pixels
#define OLED_RESET     -1 // Reset pin # (or -1 if sharing Arduino reset pin)
#define SCREEN_ADDRESS 0x3C// See datasheet for address if you are using a different one


//#define USE_TELEGRAM

#ifdef USE_TELEGRAM
// Telegram Bot configuration - Replace with your values
extern const char* telegram_bot_token;
extern const char* telegram_chat_id;
#endif


#endif //CONFIG_H

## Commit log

2020-07-20 reordering
2020-07-21 data
2020-07-21 change names
2020-08-05 save mode, colored buttons, fixed ip, temp and more fixes
2020-08-20 fix parsingm, preliminary chartjs
2020-08-21 chartjs
2020-08-23 simple example
2020-08-24 graph redraw
2020-08-24 dht data in status not always [0]
2020-09-05 fix temp, heat. fix date on graph
2020-10-01 bmp180
2020-10-02 json buffer
2020-10-03 pcb and logs
2020-11-06 fix bmp and parser alternative
2020-12-02 minmax temp hum press computed in js
2021-01-03 Update README.md
    pre-heat code
2021-01-04 preheat
2021-01-05 min no zero
2021-06-22 fix some crashes and graph
2021-06-22 refactoring
2021-07-06 schematics.pdf
2021-07-08 photos
2022-01-04 spiffs littlefs
2022-01-05 reduce log size, may cause problems
2022-01-09 clean up and websocket reconnect
2022-01-28 comment wip
2022-02-11 websocket.loop fixed. thnx cmc88
2022-04-01 added git ignore file
2022-04-01 first refactor
2022-04-03 refactor(extract includes and replace ifdef by pragma ):
2022-04-03 extract to helper file
2022-04-03 remove death code
2022-04-03 remove old wifi settings and method
2022-04-03 move example to doc folder
2022-04-03 Revert "move example to doc folder"
    This reverts commit 8f58dc12ccac79f0982fadadea4715b3d1c69bed.
2022-04-03 moved example to doc directory
2022-04-03 push defines to config file
2022-04-03 ntptimer decoupling
2022-04-03 extract to wifi module
2022-04-03 OTA module
2022-04-03 decoupling sensor devices
2022-04-03 hotfix
2022-04-03 reduce float decimal places
2022-04-06 Feat: dual compatibilities
    Hack for can works with Arduino IDE and PlatformIO at the same time
    Also documented
2023-07-19 installation photos README.md
2024-01-17 AB polarity waring
2025-07-23 cleaning for v2.0
2025-07-23 new files for v2.0
2025-07-25 home assintant discovery fixed, sensors, temp chart and more
2025-07-25 more compact ui
2025-07-29 restore ui
2025-08-09 fix timer, improved ws responsiveness, simulation mode
2025-08-09 clean
2025-08-10 reorganize sections in web
2025-08-10 simulation mode text
2025-08-12 fix timeseries, refactor sensor reading
2025-08-13 web interface instructions
2025-08-14 filemanager
2025-08-14 clean examples
2025-08-14 reorder
2025-08-15 filemanager fix
2025-08-25 Fix formatting and spacing in README.md
2025-12-22 Highlight opcode values in README examples
2025-12-22 Highlight opcode values in README
2025-12-25 Refine source/destination byte descriptions and examples
    Updated the README to clarify source/destination byte descriptions and added examples for operation codes.
2025-12-26 Clarify pong message in README
2026-01-16 Update command for Error history to ping
2026-02-10 preparing for v2.1
    Updated README with additional recommendations and clarifications regarding hardware usage, compilation instructions, and MQTT integration.
2026-02-11 Revise data package format and command documentation
    Updated the data package format and command structure in the README. Improved clarity and added examples for various commands and responses.
2026-02-11 Update README with new message formats and examples
2026-02-11 Update temperature coding and remote temp reporting details
    Clarify temperature coding and remote temperature reporting format in README.
2026-02-11 Fix formatting issue in README.md
2026-02-11 uploading files for 2.1
2026-02-11 air.ino
2026-02-28 messages async mode not to loose bytes when parsing long messages
